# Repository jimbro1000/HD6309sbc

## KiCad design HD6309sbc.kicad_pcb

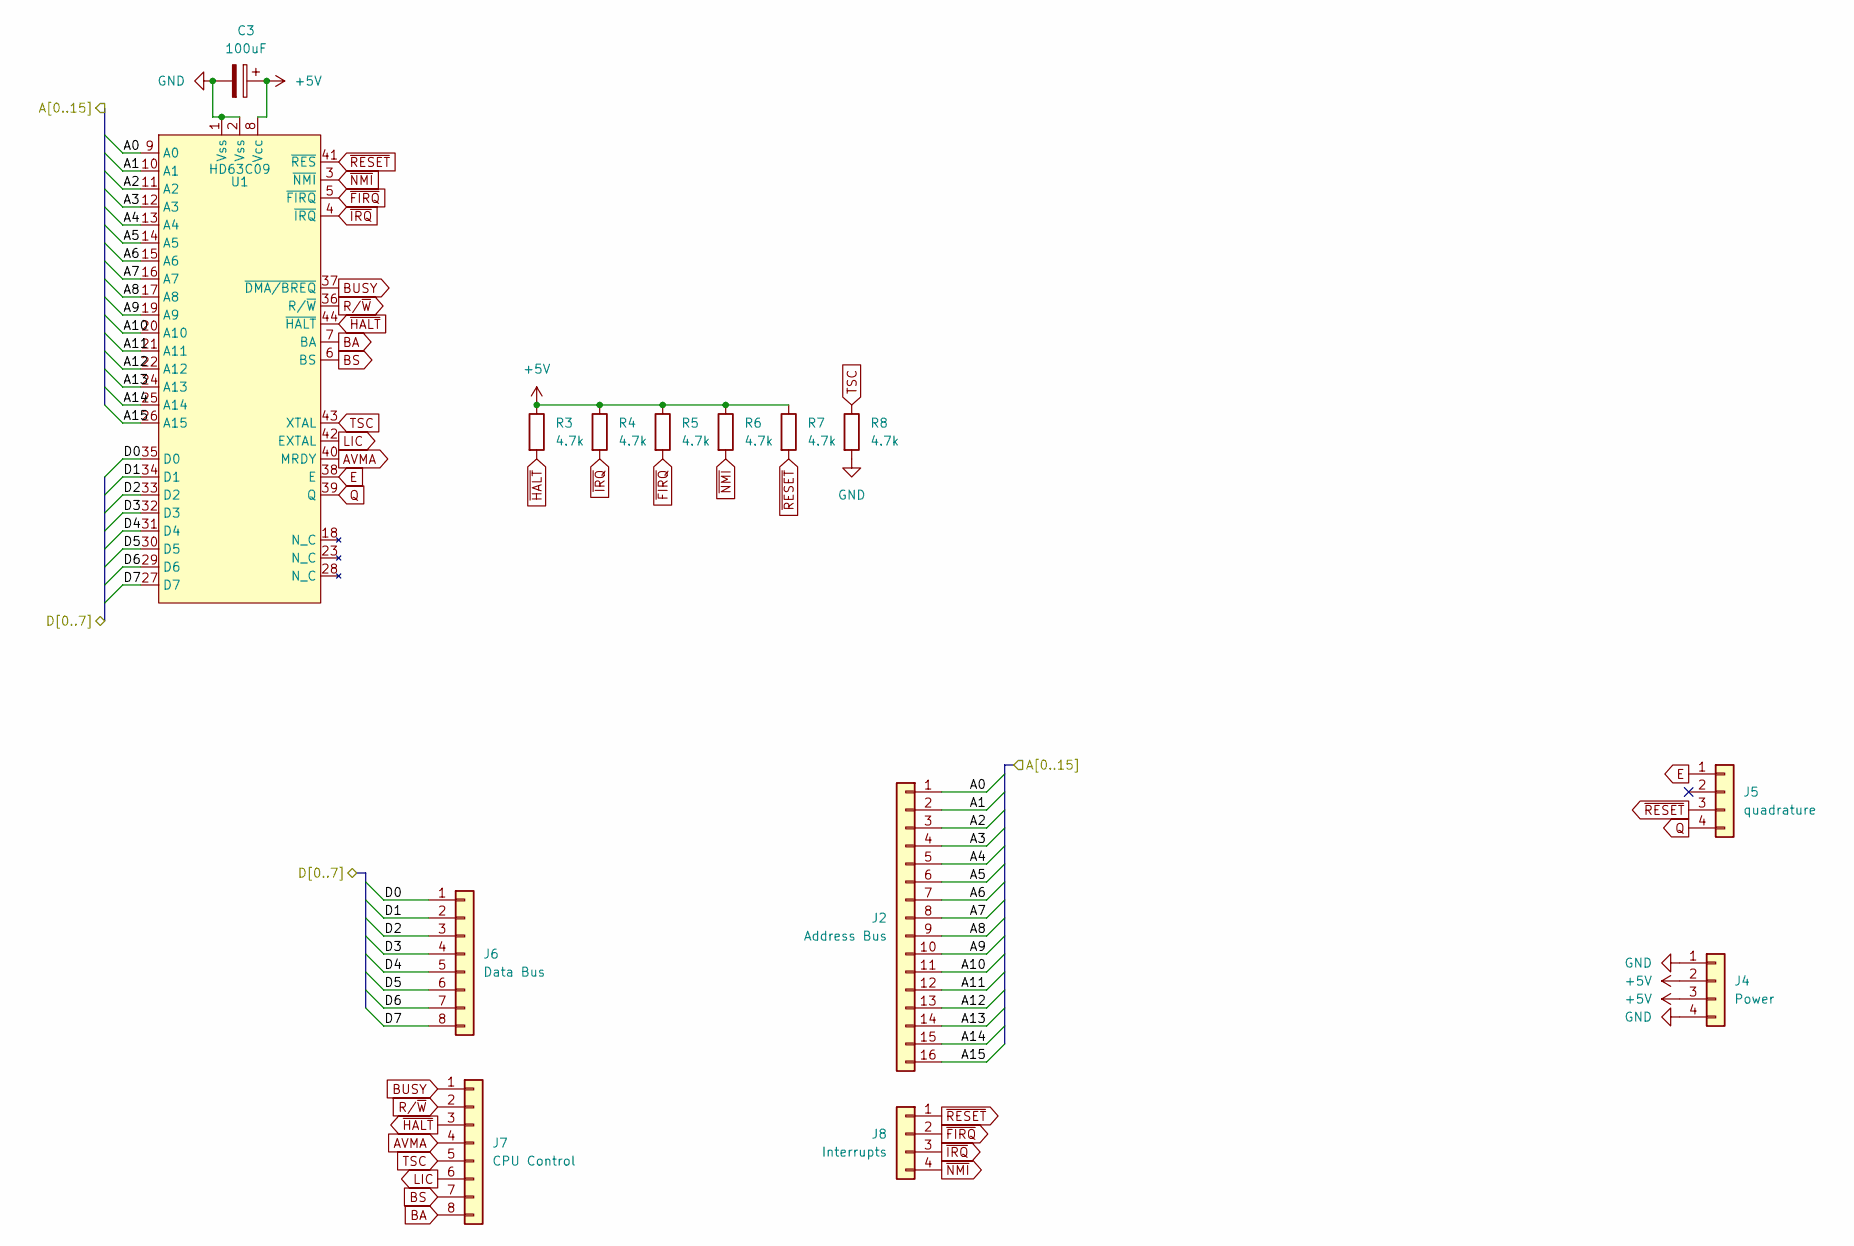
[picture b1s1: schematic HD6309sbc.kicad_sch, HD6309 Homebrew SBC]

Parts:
C3: 100uF; CP_Elec_6.3x5.8
J2: Address Bus; PinHeader_1x16_P2.54mm_Vertical
J4: Power; PinHeader_1x04_P2.54mm_Vertical
J5: quadrature; PinSocket_1x04_P2.54mm_Vertical
J6: Data Bus; PinHeader_1x08_P2.54mm_Vertical
J7: CPU Control; PinHeader_1x08_P2.54mm_Vertical
J8: Interrupts; PinHeader_1x04_P2.54mm_Vertical
R3, R4, R5, R6, R7, R8: 4.7k; R_0805_2012Metric_Pad1.20x1.40mm_HandSolder; DigiKey 2019-RK73H2ATTD2201FCT-ND
U1: HD63C09; PLCC-44_THT-Socket

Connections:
+5V: C3.1, J4.2, J4.3, R3.1, R4.1, R5.1, R6.1, R7.1, U1.8 (Vcc)
/A0: J2.1, U1.9 (A0)
/A1: J2.2, U1.10 (A1)
/A2: J2.3, U1.11 (A2)
/A3: J2.4, U1.12 (A3)
/A4: J2.5, U1.13 (A4)
/A5: J2.6, U1.14 (A5)
/A6: J2.7, U1.15 (A6)
/A7: J2.8, U1.16 (A7)
/A8: J2.9, U1.17 (A8)
/A9: J2.10, U1.19 (A9)
/A10: J2.11, U1.20 (A10)
/A11: J2.12, U1.21 (A11)
/A12: J2.13, U1.22 (A12)
/A13: J2.14, U1.24 (A13)
/A14: J2.15, U1.25 (A14)
/A15: J2.16, U1.26 (A15)
/D0: J6.1, U1.35 (D0)
/D1: J6.2, U1.34 (D1)
/D2: J6.3, U1.33 (D2)
/D3: J6.4, U1.32 (D3)
/D4: J6.5, U1.31 (D4)
/D5: J6.6, U1.30 (D5)
/D6: J6.7, U1.29 (D6)
/D7: J6.8, U1.27 (D7)
AVMA: J7.4, U1.40 (MRDY)
BA: J7.8, U1.7 (BA)
BS: J7.7, U1.6 (BS)
BUSY: J7.1, U1.37 (~DMA/BREQ)
E: J5.1, U1.38 (E)
GND: C3.2, J4.1, J4.4, R8.2, U1.1 (Vss), U1.2 (Vss)
LIC: J7.6, U1.42 (EXTAL)
Q: J5.4, U1.39 (Q)
R/~W: J7.2, U1.36 (R/~W)
TSC: J7.5, R8.1, U1.43 (XTAL)
~FIRQ: J8.2, R5.2, U1.5 (~FIRQ)
~HALT: J7.3, R3.2, U1.44 (~HALT)
~IRQ: J8.3, R4.2, U1.4 (~IRQ)
~NMI: J8.4, R6.2, U1.3 (~NMI)
~RESET: J5.3, J8.1, R7.2, U1.41 (~RES)

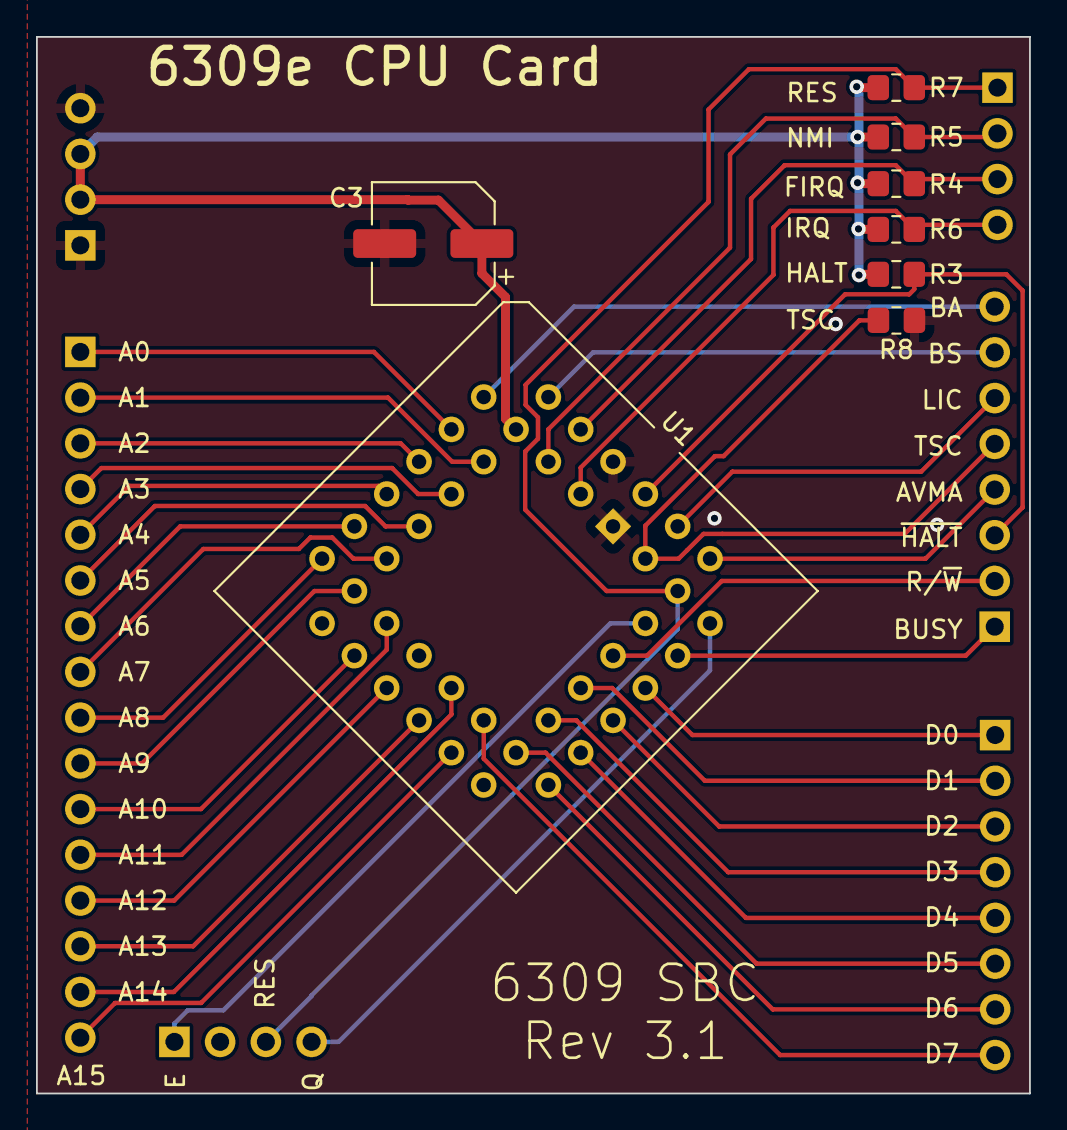
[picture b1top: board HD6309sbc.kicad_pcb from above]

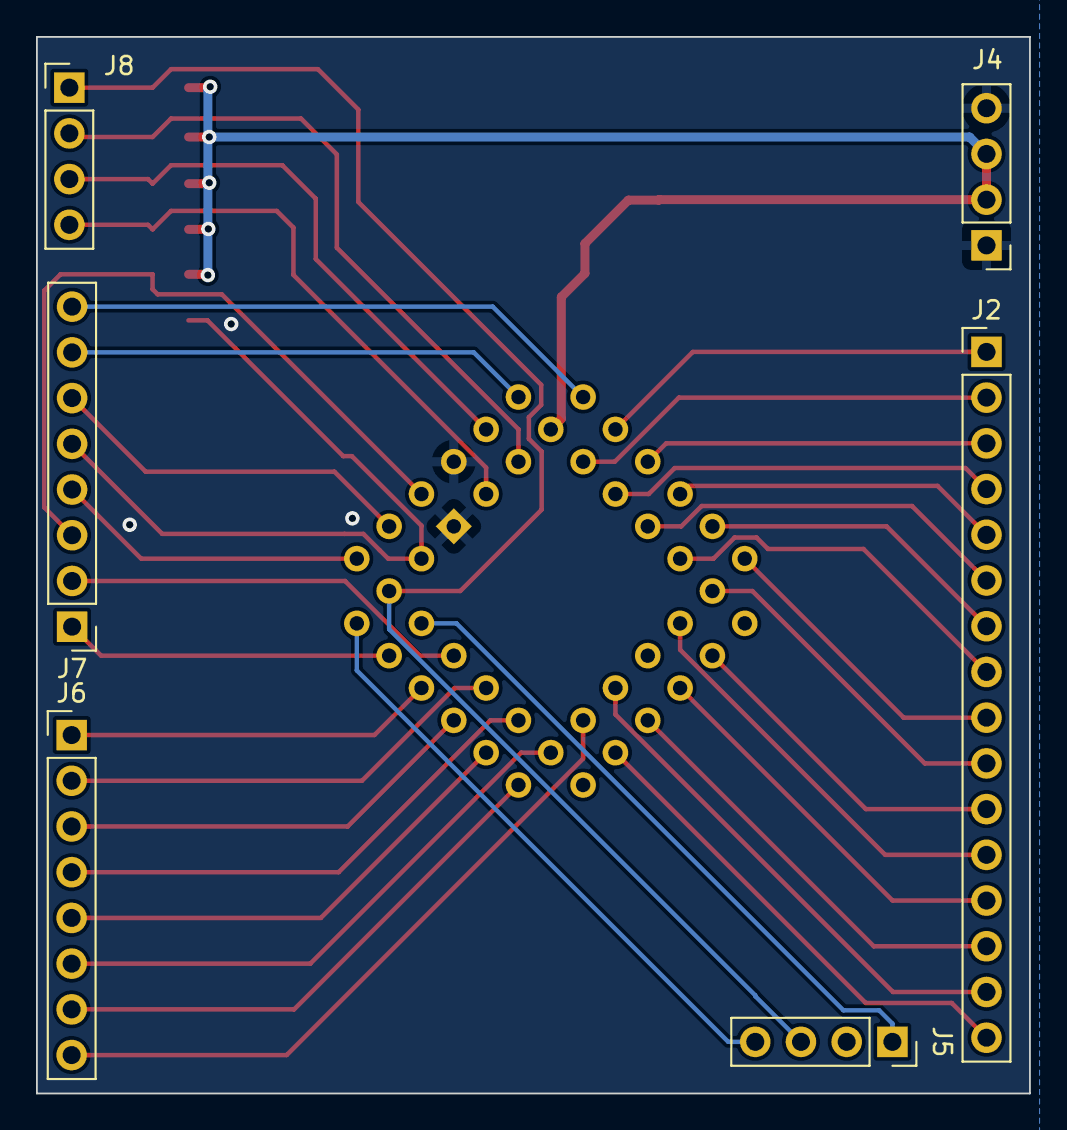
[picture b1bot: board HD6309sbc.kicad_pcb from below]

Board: 2 copper layers, 55.2 x 58.7 mm, 14 parts (6 on the bottom side), 40 nets.

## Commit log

2022-10-04 add paged memory
2022-10-05 add power routing
2022-10-05 move rom for clearance
2022-10-05 rearrange components for routing
2022-10-05 reduce component count
2022-10-05 correct memory page addressing
2022-10-06 move paged memory to external board
2022-10-06 add bom
2022-10-08 modify address logic for mapped registers
2022-11-06 update readme to help find related projects
2022-11-06 generate production
2023-01-15 fixes
2023-01-27 set reset cap value
2023-01-27 rework traces
2023-02-01 use handsolder pads
2023-02-01 improve keepout around crystal
2023-02-16 convert to discrete clock
2023-02-23 add diagnostics port
2023-02-23 use 10 segment led bar
2023-02-23 fix readme typo
2023-02-23 fix readme typo the other way
2023-02-24 tidy up component placing
2023-03-07 fix rom footprint
2023-03-07 update interactive bom
2023-04-08 add test code
2023-04-08 refine test1
2023-04-08 shorthand batch file for assembly
2023-04-08 add memory handling
2023-04-09 extend testrom1
2023-04-11 board refresh
2023-04-11 extend testkit1 with interrupt and page handling
2023-04-11 fix testrom1
2023-04-11 add linux tasks
2023-04-11 tweak testrom1
2023-04-11 add revised output
2023-04-23 add pia and keyboard
2023-04-24 buffer keyboard input
2023-04-26 6809 safe pia0 test exercise
2023-04-27 revise pia test rom
2023-05-17 Refine reset circuit
2024-04-11 convert to new format
2024-04-11 disambiguate register address
2024-04-15 tighten up tracing
2025-05-12 clean up before redesign
